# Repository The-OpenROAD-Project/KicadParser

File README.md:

# KicadParser

This is a KiCad file importer/exporter, database, and DRC checker.

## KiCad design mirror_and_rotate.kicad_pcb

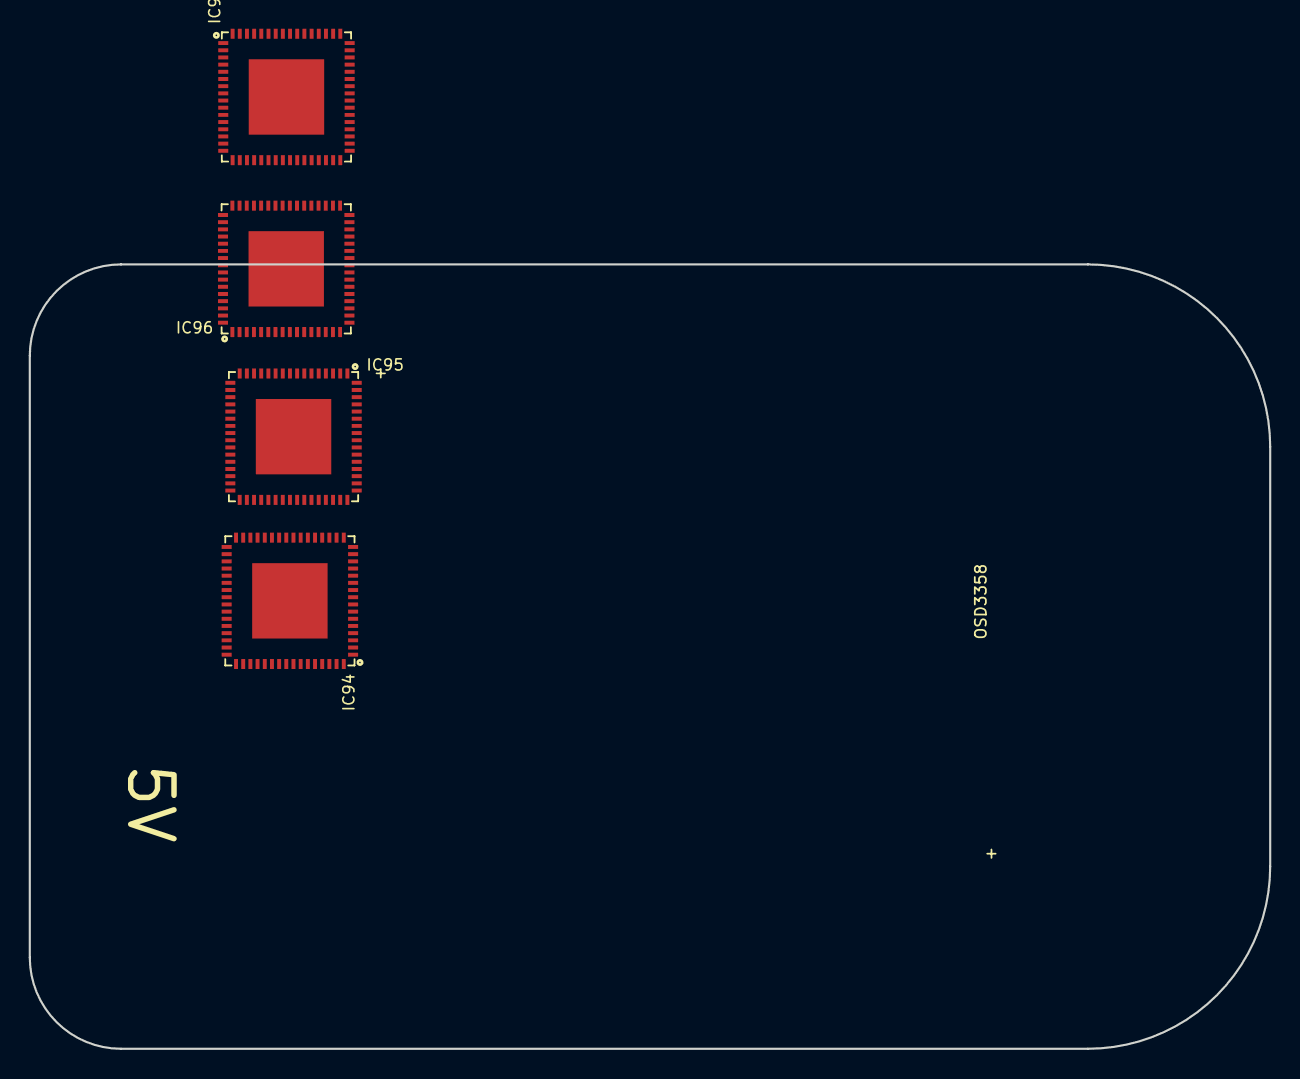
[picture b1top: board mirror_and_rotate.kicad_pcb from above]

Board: 6 copper layers, 86.4 x 54.6 mm, 8 parts (0 on the bottom side), 2 nets, no tracks yet.

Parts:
IC91, IC92, IC93, IC94, IC95, IC96, IC97, IC98: TDA19988BHN/C1,557; SOT804-4(NXP)

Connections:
GND: IC98.8, IC98.9, IC98.16, IC98.17, IC98.18, IC98.19, IC98.53, IC98.54, IC98.61, IC98.62, IC98.63, IC98.65
HDMI_1V8: IC98.5, IC98.14, IC98.29, IC98.35, IC98.36, IC98.41, IC98.46, IC98.47, IC98.48, IC98.55

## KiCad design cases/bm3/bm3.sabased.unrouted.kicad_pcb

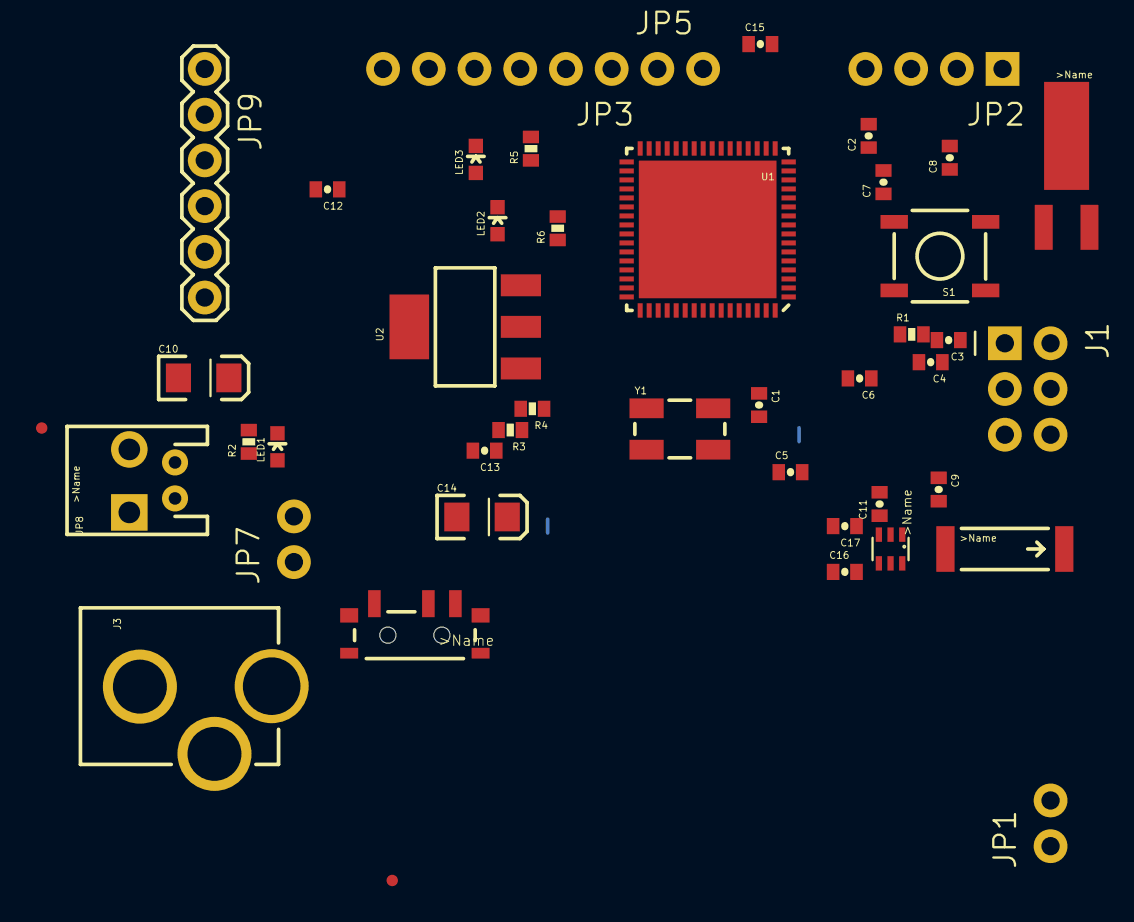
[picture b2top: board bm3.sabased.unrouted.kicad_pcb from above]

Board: 2 copper layers, 48 parts (0 on the bottom side), 41 nets, no tracks yet.

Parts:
A1: ANTENNA2SMD5; ANTENNA-CHIP5
B1: 748421245; BALUN
C1, C2, C3, C4, C12: 1uF; 0402-CAP
C5, C6, C7, C8: 12pF; 0402-CAP
C9: 0.75pF; 0402-CAP
C10, C14: 10uF; EIA3216
C11: 22pF; 0402-CAP
C13, C15: 0.1uF; 0402-CAP
C16, C17: JUMP; 0402-CAP
FID1, FID2: FIDUCIALUFIDUCIAL; MICRO-FIDUCIAL
J1: ISP; 2X3-NS
J3: POWER_JACKPTH_LOCK; POWER_JACK_PTH_LOCK
JP1, JP5, JP7: 1X02_NO_SILK
JP2: 1X04_NO_SILK
JP3: 1X06_NS
JP6: JST-2-PTH
JP8: SCREWTERMINAL-3.5MM-2-NS
JP9: FTDI; FTDI_BASIC
LED1: RED; LED-0603
LED2, LED3: GREEN; LED-0603
R1: 10k; 0402-RES
R2: 1k; 0402-RES
R3: 240; 0402-RES
R4: 390; 0402-RES
R5, R6: 330; 0402-RES
S1: TACTILE_SWITCH_SMD
S2: SWITCH-SPST-SMD-A
SJ1, SJ2: SJ_2S-TRACE
U1: ATMEGA128RFA1; QFN-64
U2: LM1117; SOT223
Y1: 16MHz; CRYSTAL-SMD-5X3
Y2: 32.768kHz; CRYSTAL-32KHZ-SMD

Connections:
3.3V: C3.1, C4.1, C10.A, C12.1, J1.2, JP9.VCC, R1.2, R2.2, R3.2, U1.23, U1.34, U1.44, U1.54, U1.59, U2.2
A6: JP1.1, U1.5
A7: JP1.2, U1.6
AVDD: C1.1, U1.60
CLKI: JP5.1, SJ1.2, U1.33
DTR: C15.1, JP9.DTR
DVDD: C2.1, U1.21, U1.22
FB: R3.1, R4.2, U2.1
GND: B1.5, C1.2, C2.2, C3.2, C4.2, C5.2, C6.2, C7.2, C8.2, C9.1, C10.C, C11.2, C12.2, C13.2, C14.C, J1.6, J3.GND, J3.GNDBREAK, JP6.1, JP7.1, JP8.1, JP9.GND, LED1.C, LED2.C, LED3.C, R4.1, S1.3, SJ1.1, SJ2.1, U1.7, U1.10, U1.20, U1.24, U1.35, U1.45, U1.55, U1.58, U1.61, U1.65
unnamed: LED1.A, R2.1
unnamed: C5.1, U1.57, Y1.3
unnamed: C6.1, U1.56, Y1.1
unnamed: C7.1, U1.18, Y2.X1
unnamed: C8.1, U1.17, Y2.X2
unnamed: B1.2, C11.1
unnamed: LED3.A, R5.1
unnamed: J3.PWR, JP6.2, JP7.2, JP8.2, S2.2
unnamed: B1.4, C16.2
unnamed: B1.3, C17.1
unnamed: LED2.A, R6.1
PB6: R5.2, U1.42
PB7: R6.2, U1.43
PD4: JP3.3, U1.29
PD5: JP3.4, U1.30
PD6: JP3.5, U1.31
PD7: JP3.6, U1.32
PG0: JP2.1, U1.14
PG1: JP2.2, U1.15
PG2: JP2.3, U1.16
PG5: JP2.4, U1.19
RESET: C15.2, J1.5, R1.1, S1.1, U1.12
RFANT: A1.FEED, B1.1, C9.2
RFN: C17.2, U1.9
RFP: C16.1, U1.8
RX0: JP9.TXO, U1.46
RX1: JP3.1, U1.27
SCK: J1.3, U1.37
TST: JP5.2, SJ2.2, U1.11
TX0: JP9.RXI, U1.47
TX1: JP3.2, U1.28
VCC: C13.1, C14.A, S2.1, U2.3

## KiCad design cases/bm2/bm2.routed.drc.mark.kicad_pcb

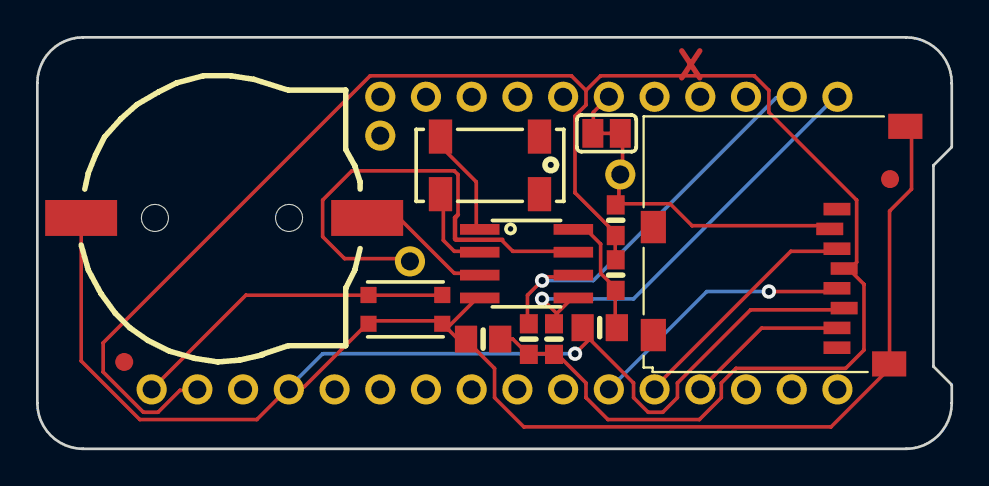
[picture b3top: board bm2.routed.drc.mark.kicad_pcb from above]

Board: 2 copper layers, 50.8 x 22.9 mm, 19 parts (0 on the bottom side), 15 nets.

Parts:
B1: cr1220; CR1220-2
C1, C2: 10uF; 0805-NO
FID1, FID2: FIDUCIAL_1MM
IC1: PCF8523T; SOIC8_150MIL
INT1: 1X01_ROUND
JP1: 1X11_ROUND
JP2: 1X16_ROUND
JP3: 1X01_ROUND
R1, R2: 10K; 0603-NO
R3: 100K; 0603-NO
R4: 1K; 0603-NO
SDCS: 1X01_ROUND
SJ1: SOLDERJUMPER_CLOSEDWIRE
SW1: KMR2; BTN_KMR2_4.6X2.8
X4: microsd; MICROSD
Y1: 32khz; CRYSTAL_8X3.8

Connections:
+3V3: C2.1, JP2.15, R1.2, R2.2, R3.2, R4.1, X4.4
CR1220: B1.+, IC1.3
CS: JP1.6, SJ1.1
GND: B1.-, C1.2, C2.2, IC1.4, JP2.13, SW1.A, SW1.A', X4.6, X4.MT1, X4.MT2
INT1: IC1.7, INT1.1
MISO: JP2.4, X4.7
MOSI: JP2.5, X4.3
unnamed: C1.1, IC1.8, R4.2
unnamed: IC1.1, Y1.P$4
unnamed: IC1.2, Y1.P$1
RESET: JP2.16, SW1.B, SW1.B'
SCK: JP2.6, X4.5
SCL: IC1.6, JP1.10, R2.1
SDA: IC1.5, JP1.11, R1.1
SD_CS: R3.1, SDCS.1, SJ1.2, X4.2

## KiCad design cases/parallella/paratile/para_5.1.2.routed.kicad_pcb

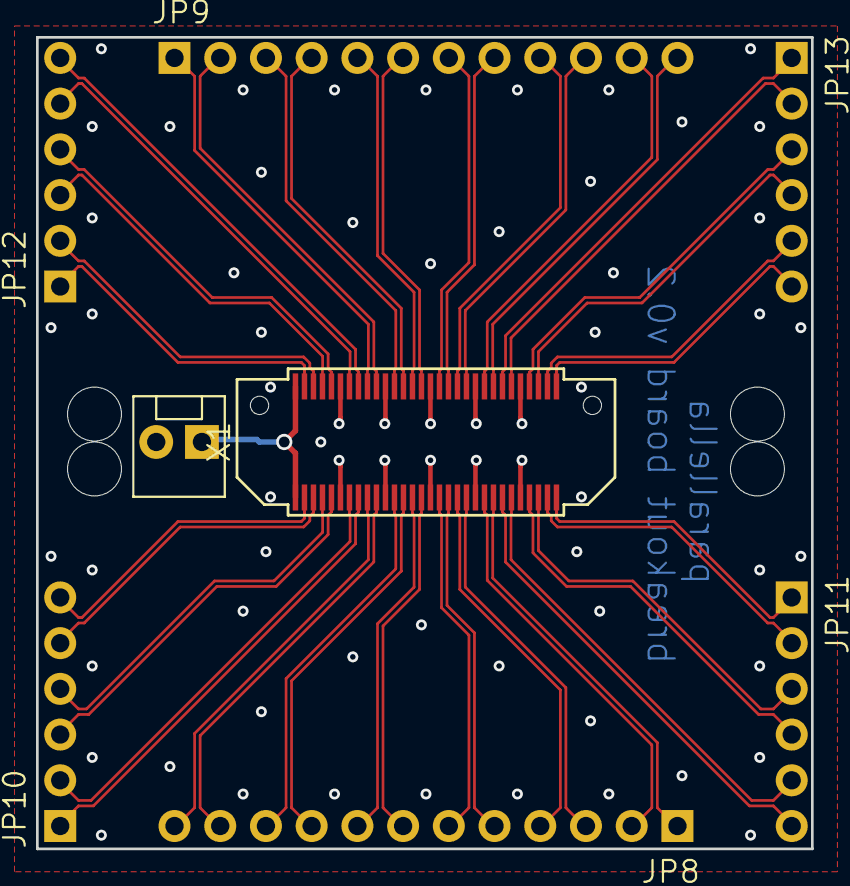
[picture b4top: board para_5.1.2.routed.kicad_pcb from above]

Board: 2 copper layers, 43.1 x 45.1 mm, 13 parts (0 on the bottom side), 50 nets.

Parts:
@HOLE0, @HOLE1, @HOLE2, @HOLE3: (no value)
C2: CAP0805; 0805
JP7: M02POLAR; MOLEX-1X2
JP8, JP9: PINHD-1X12-CB; 1X12-CB
JP10, JP11, JP12, JP13: PINHD-1X6CB; 1X06-CLEANBIG
X1: BTH-030-XX-X-D-A

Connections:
GND: C2.2, JP7.2, X1.11, X1.12, X1.21, X1.22, X1.31, X1.32, X1.41, X1.42, X1.51, X1.52
unnamed: JP8.1, X1.46
unnamed: JP8.2, X1.44
unnamed: JP8.3, X1.40
unnamed: JP8.4, X1.38
unnamed: JP8.5, X1.36
unnamed: JP8.6, X1.34
unnamed: JP8.7, X1.30
unnamed: JP8.8, X1.28
unnamed: JP8.9, X1.26
unnamed: JP8.10, X1.24
unnamed: JP8.11, X1.20
unnamed: JP8.12, X1.18
unnamed: JP9.1, X1.17
unnamed: JP9.2, X1.19
unnamed: JP9.3, X1.23
unnamed: JP9.4, X1.25
unnamed: JP9.5, X1.27
unnamed: JP9.6, X1.29
unnamed: JP9.7, X1.33
unnamed: JP9.8, X1.35
unnamed: JP9.9, X1.37
unnamed: JP9.10, X1.39
unnamed: JP9.11, X1.43
unnamed: JP9.12, X1.45
unnamed: JP10.1, X1.16
unnamed: JP10.2, X1.14
unnamed: JP10.3, X1.10
unnamed: JP10.4, X1.8
unnamed: JP10.5, X1.6
unnamed: JP10.6, X1.4
unnamed: JP11.1, X1.60
unnamed: JP11.2, X1.58
unnamed: JP11.3, X1.56
unnamed: JP11.4, X1.54
unnamed: JP11.5, X1.50
unnamed: JP11.6, X1.48
unnamed: JP12.1, X1.3
unnamed: JP12.2, X1.5
unnamed: JP12.3, X1.7
unnamed: JP12.4, X1.9
unnamed: JP12.5, X1.13
unnamed: JP12.6, X1.15
unnamed: JP13.1, X1.47
unnamed: JP13.2, X1.49
unnamed: JP13.3, X1.53
unnamed: JP13.4, X1.55
unnamed: JP13.5, X1.57
unnamed: JP13.6, X1.59
VCC: C2.1, JP7.1, X1.1, X1.2

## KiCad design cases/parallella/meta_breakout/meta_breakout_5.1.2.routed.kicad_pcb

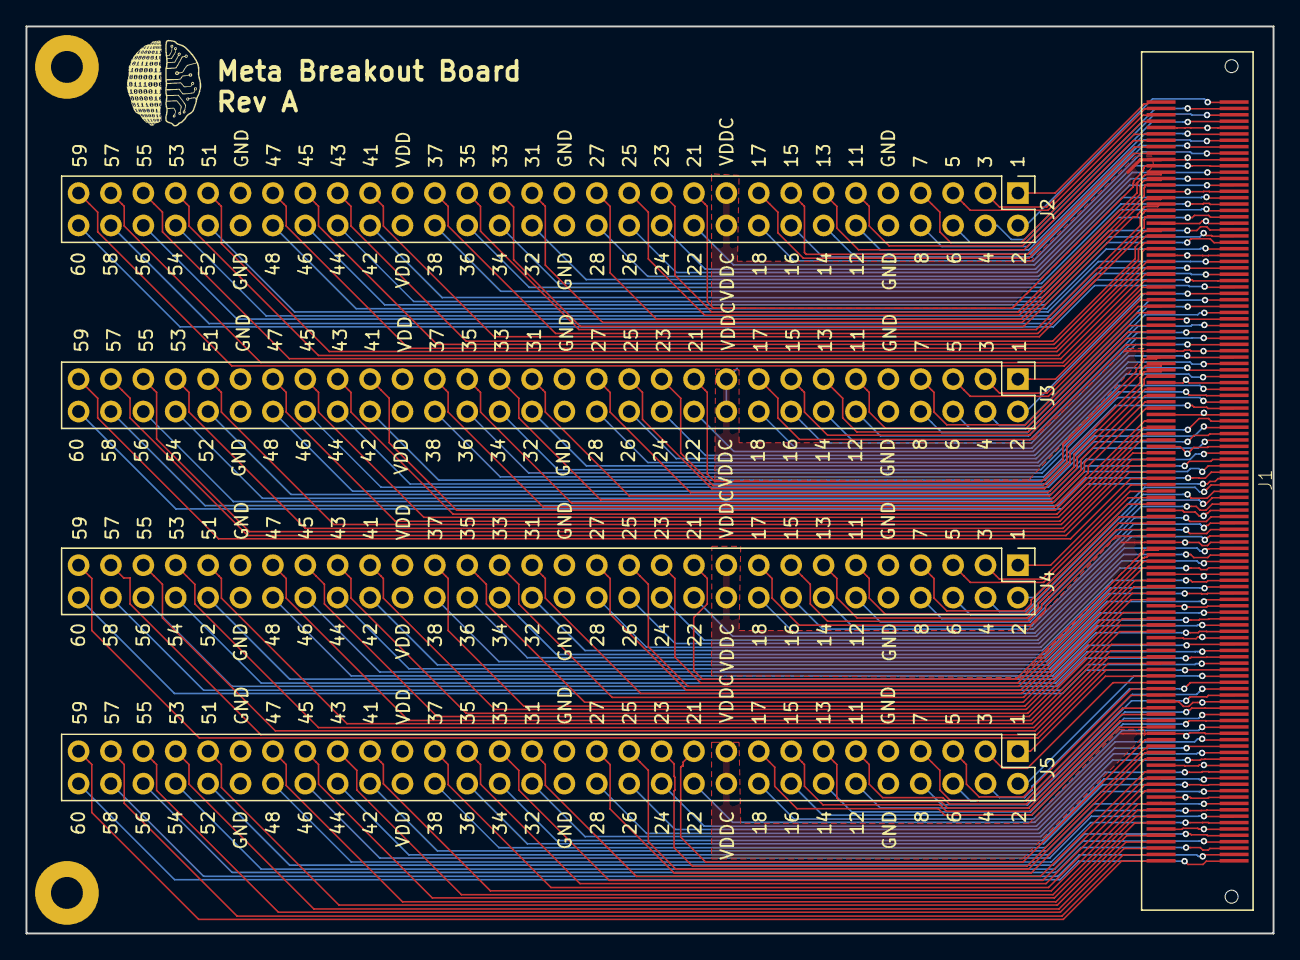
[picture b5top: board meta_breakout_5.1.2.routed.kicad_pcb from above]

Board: 4 copper layers, 97.8 x 71.1 mm, 5 parts (0 on the bottom side), 209 nets.

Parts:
J1: BSH-120; BSH-120-01-X-D-A
J2, J3, J4, J5: Conn_02x30_Odd_Even; PinHeader_2x30_P2.54mm_Vertical

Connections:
/CTRL_IN0: J1.59, J2.59
/CTRL_IN1: J1.119, J3.59
/CTRL_IN2: J1.179, J4.59
/CTRL_IN3: J1.239, J5.59
/CTRL_OUT0: J1.60, J2.60
/CTRL_OUT1: J1.120, J3.60
/CTRL_OUT2: J1.180, J4.60
/CTRL_OUT3: J1.240, J5.60
/DATA_IN_N0: J1.21, J2.21
/DATA_IN_N1: J1.25, J2.25
/DATA_IN_N2: J1.31, J2.31
/DATA_IN_N3: J1.35, J2.35
/DATA_IN_N4: J1.41, J2.41
/DATA_IN_N5: J1.45, J2.45
/DATA_IN_N6: J1.51, J2.51
/DATA_IN_N7: J1.55, J2.55
/DATA_IN_N8: J1.81, J3.21
/DATA_IN_N9: J1.85, J3.25
/DATA_IN_N10: J1.91, J3.31
/DATA_IN_N11: J1.95, J3.35
/DATA_IN_N12: J1.101, J3.41
/DATA_IN_N13: J1.105, J3.45
/DATA_IN_N14: J1.111, J3.51
/DATA_IN_N15: J1.115, J3.55
/DATA_IN_N16: J1.141, J4.21
/DATA_IN_N17: J1.145, J4.25
/DATA_IN_N18: J1.151, J4.31
/DATA_IN_N19: J1.155, J4.35
/DATA_IN_N20: J1.161, J4.41
/DATA_IN_N21: J1.165, J4.45
/DATA_IN_N22: J1.171, J4.51
/DATA_IN_N23: J1.175, J4.55
/DATA_IN_N24: J1.201, J5.21
/DATA_IN_N25: J1.205, J5.25
/DATA_IN_N26: J1.211, J5.31
/DATA_IN_N27: J1.215, J5.35
/DATA_IN_N28: J1.221, J5.41
/DATA_IN_N29: J1.225, J5.45
/DATA_IN_N30: J1.231, J5.51
/DATA_IN_N31: J1.235, J5.55
/DATA_IN_P0: J1.23, J2.23
/DATA_IN_P1: J1.27, J2.27
/DATA_IN_P2: J1.33, J2.33
/DATA_IN_P3: J1.37, J2.37
/DATA_IN_P4: J1.43, J2.43
/DATA_IN_P5: J1.47, J2.47
/DATA_IN_P6: J1.53, J2.53
/DATA_IN_P7: J1.57, J2.57
/DATA_IN_P8: J1.83, J3.23
/DATA_IN_P9: J1.87, J3.27
/DATA_IN_P10: J1.93, J3.33
/DATA_IN_P11: J1.97, J3.37
/DATA_IN_P12: J1.103, J3.43
/DATA_IN_P13: J1.107, J3.47
/DATA_IN_P14: J1.113, J3.53
/DATA_IN_P15: J1.117, J3.57
/DATA_IN_P16: J1.143, J4.23
/DATA_IN_P17: J1.147, J4.27
/DATA_IN_P18: J1.153, J4.33
/DATA_IN_P19: J1.157, J4.37
/DATA_IN_P20: J1.163, J4.43
/DATA_IN_P21: J1.167, J4.47
/DATA_IN_P22: J1.173, J4.53
/DATA_IN_P23: J1.177, J4.57
/DATA_IN_P24: J1.203, J5.23
/DATA_IN_P25: J1.207, J5.27
/DATA_IN_P26: J1.213, J5.33
/DATA_IN_P27: J1.217, J5.37
/DATA_IN_P28: J1.223, J5.43
/DATA_IN_P29: J1.227, J5.47
/DATA_IN_P30: J1.233, J5.53
/DATA_IN_P31: J1.237, J5.57
/DATA_OUT_N0: J1.22, J2.22
/DATA_OUT_N1: J1.26, J2.26
/DATA_OUT_N2: J1.32, J2.32
/DATA_OUT_N3: J1.36, J2.36
/DATA_OUT_N4: J1.42, J2.42
/DATA_OUT_N5: J1.46, J2.46
/DATA_OUT_N6: J1.52, J2.52
/DATA_OUT_N7: J1.56, J2.56
/DATA_OUT_N8: J1.82, J3.22
/DATA_OUT_N9: J1.86, J3.26
/DATA_OUT_N10: J1.92, J3.32
/DATA_OUT_N11: J1.96, J3.36
/DATA_OUT_N12: J1.102, J3.42
/DATA_OUT_N13: J1.106, J3.46
/DATA_OUT_N14: J1.112, J3.52
/DATA_OUT_N15: J1.116, J3.56
/DATA_OUT_N16: J1.142, J4.22
/DATA_OUT_N17: J1.146, J4.26
/DATA_OUT_N18: J1.152, J4.32
/DATA_OUT_N19: J1.156, J4.36
/DATA_OUT_N20: J1.162, J4.42
/DATA_OUT_N21: J1.166, J4.46
/DATA_OUT_N22: J1.172, J4.52
/DATA_OUT_N23: J1.176, J4.56
/DATA_OUT_N24: J1.202, J5.22
/DATA_OUT_N25: J1.206, J5.26
/DATA_OUT_N26: J1.212, J5.32
/DATA_OUT_N27: J1.216, J5.36
/DATA_OUT_N28: J1.222, J5.42
/DATA_OUT_N29: J1.226, J5.46
/DATA_OUT_N30: J1.232, J5.52
/DATA_OUT_N31: J1.236, J5.56
/DATA_OUT_P0: J1.24, J2.24
/DATA_OUT_P1: J1.28, J2.28
/DATA_OUT_P2: J1.34, J2.34
/DATA_OUT_P3: J1.38, J2.38
/DATA_OUT_P4: J1.44, J2.44
/DATA_OUT_P5: J1.48, J2.48
/DATA_OUT_P6: J1.54, J2.54
/DATA_OUT_P7: J1.58, J2.58
/DATA_OUT_P8: J1.84, J3.24
/DATA_OUT_P9: J1.88, J3.28
/DATA_OUT_P10: J1.94, J3.34
/DATA_OUT_P11: J1.98, J3.38
/DATA_OUT_P12: J1.104, J3.44
/DATA_OUT_P13: J1.108, J3.48
/DATA_OUT_P14: J1.114, J3.54
/DATA_OUT_P15: J1.118, J3.58
/DATA_OUT_P16: J1.144, J4.24
/DATA_OUT_P17: J1.148, J4.28
/DATA_OUT_P18: J1.154, J4.34
/DATA_OUT_P19: J1.158, J4.38
/DATA_OUT_P20: J1.164, J4.44
/DATA_OUT_P21: J1.168, J4.48
/DATA_OUT_P22: J1.174, J4.54
/DATA_OUT_P23: J1.178, J4.58
/DATA_OUT_P24: J1.204, J5.24
/DATA_OUT_P25: J1.208, J5.28
/DATA_OUT_P26: J1.214, J5.34
/DATA_OUT_P27: J1.218, J5.38
/DATA_OUT_P28: J1.224, J5.44
/DATA_OUT_P29: J1.228, J5.48
/DATA_OUT_P30: J1.234, J5.54
/DATA_OUT_P31: J1.238, J5.58
/FRAME_IN_N0: J1.5, J2.5
/FRAME_IN_N1: J1.65, J3.5
/FRAME_IN_N2: J1.125, J4.5
/FRAME_IN_N3: J1.185, J5.5
/FRAME_IN_P0: J1.7, J2.7
/FRAME_IN_P1: J1.67, J3.7
/FRAME_IN_P2: J1.127, J4.7
/FRAME_IN_P3: J1.187, J5.7
/FRAME_OUT_N0: J1.6, J2.6
/FRAME_OUT_N1: J1.66, J3.6
/FRAME_OUT_N2: J1.126, J4.6
/FRAME_OUT_N3: J1.186, J5.6
/FRAME_OUT_P0: J1.8, J2.8
/FRAME_OUT_P1: J1.68, J3.8
/FRAME_OUT_P2: J1.128, J4.8
/FRAME_OUT_P3: J1.188, J5.8
/GND: J1.9, J1.10, J1.29, J1.30, J1.49, J1.50, J1.69, J1.70, J1.89, J1.90, J1.109, J1.110, J1.129, J1.130, J1.149, J1.150, J1.169, J1.170, J1.189, J1.190, J1.209, J1.210, J1.229, J1.230, J2.9, J2.10, J2.29, J2.30, J2.49, J2.50, J3.9, J3.10, J3.29, J3.30, J3.49, J3.50, J4.9, J4.10, J4.29, J4.30, J4.49, J4.50, J5.9, J5.10, J5.29, J5.30, J5.49, J5.50
/LCLK_IN_N0: J1.1, J2.1
/LCLK_IN_N1: J1.61, J3.1
/LCLK_IN_N2: J1.121, J4.1
/LCLK_IN_N3: J1.181, J5.1
/LCLK_IN_P0: J1.3, J2.3
/LCLK_IN_P1: J1.63, J3.3
/LCLK_IN_P2: J1.123, J4.3
/LCLK_IN_P3: J1.183, J5.3
/LCLK_OUT_N0: J1.2, J2.2
/LCLK_OUT_N1: J1.62, J3.2
/LCLK_OUT_N2: J1.122, J4.2
/LCLK_OUT_N3: J1.182, J5.2
/LCLK_OUT_P0: J1.4, J2.4
/LCLK_OUT_P1: J1.64, J3.4
/LCLK_OUT_P2: J1.124, J4.4
/LCLK_OUT_P3: J1.184, J5.4
/VDD0: J1.19, J1.20, J2.19, J2.20
/VDD1: J1.79, J1.80, J3.19, J3.20
/VDD2: J1.139, J1.140, J4.19, J4.20
/VDD3: J1.199, J1.200, J5.19, J5.20
/VDDIO0: J1.39, J1.40, J2.39, J2.40
/VDDIO1: J1.99, J1.100, J3.39, J3.40
/VDDIO2: J1.159, J1.160, J4.39, J4.40
/VDDIO3: J1.219, J1.220, J5.39, J5.40
/WAIT_RD_IN_N0: J1.16, J2.16
/WAIT_RD_IN_N1: J1.76, J3.16
/WAIT_RD_IN_N2: J1.136, J4.16
/WAIT_RD_IN_N3: J1.196, J5.16
/WAIT_RD_IN_P0: J1.18, J2.18
/WAIT_RD_IN_P1: J1.78, J3.18
/WAIT_RD_IN_P2: J1.138, J4.18
/WAIT_RD_IN_P3: J1.198, J5.18
/WAIT_RD_OUT_N0: J1.15, J2.15
/WAIT_RD_OUT_N1: J1.75, J3.15
/WAIT_RD_OUT_N2: J1.135, J4.15
/WAIT_RD_OUT_N3: J1.195, J5.15
/WAIT_RD_OUT_P0: J1.17, J2.17
/WAIT_RD_OUT_P1: J1.77, J3.17
/WAIT_RD_OUT_P2: J1.137, J4.17
/WAIT_RD_OUT_P3: J1.197, J5.17
/WAIT_WR_IN_N0: J1.12, J2.12
/WAIT_WR_IN_N1: J1.72, J3.12
/WAIT_WR_IN_N2: J1.132, J4.12
/WAIT_WR_IN_N3: J1.192, J5.12
/WAIT_WR_IN_P0: J1.14, J2.14
/WAIT_WR_IN_P1: J1.74, J3.14
/WAIT_WR_IN_P2: J1.134, J4.14
/WAIT_WR_IN_P3: J1.194, J5.14
/WAIT_WR_OUT_N0: J1.11, J2.11
/WAIT_WR_OUT_N1: J1.71, J3.11
/WAIT_WR_OUT_N2: J1.131, J4.11
/WAIT_WR_OUT_N3: J1.191, J5.11
/WAIT_WR_OUT_P0: J1.13, J2.13
/WAIT_WR_OUT_P1: J1.73, J3.13
/WAIT_WR_OUT_P2: J1.133, J4.13
/WAIT_WR_OUT_P3: J1.193, J5.13

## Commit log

2019-08-13 addAPIs
2019-08-13 addMakefile
2019-08-16 Add router helping APIs
2019-08-16 Overload net::getId()
2019-08-16 get PcbRouterInfo based on netId
2019-09-04 Use Cmake and restructure folders
2019-09-05 Clean the CMakeLists.txt
2019-09-05 -Wall option in CMakeLists.txt
2019-09-07 add segment/via; fix bug for boundary/rotation
2019-09-09 indent
2019-09-09 add license
2019-09-12 refactor
2019-09-12 restructure
2019-09-13 VS Code beautifier and input file extension checking
2019-09-13 VS Code beautifier, util.h updates and basic file extension checking
2019-09-13 Update #define guard
2019-09-13 add testcases
2019-09-14 Minor refactors
2019-09-14 Fix warning messages
2019-09-16 Refactor and code review
2019-09-16 Add new artificial testcase for router testing Vias and Rip-up & Reroute
2019-09-19 Add APIs and major refactor
2019-09-20 add via and segment header
2019-09-20 modify APIs
2019-09-20 Add more APIs and minor refactors
2019-09-21 APIs and minor refactors
2019-09-23 Add segments and vias
2019-09-23 Minor refactors on APIs
2019-09-24 Add APIs for pads' width and height
2019-09-24 Update mymath.h to point.h and use template
2019-09-25 Add APIs in point.h
2019-09-25 unconnected pins
2019-09-25 Fix template type T
2019-09-26 boundary and octagon
2019-09-27 add testcase
2019-09-28 test meta_breakout, fix seg fault
2019-09-28 Add parallella testcases in .kicad_pcb format
2019-09-28 Add three more parallella testcases
2019-09-28 Change parallella files into routed and unrouted ones
2019-09-28 0.1 version of printing out .kicad_pcb
2019-09-28 fix via for parallella
2019-09-30 Fix layer from Component to Instance and from Padstack to Pin
2019-10-03 Deprecate the layers information in Pin
2019-10-03 modify shape func
2019-10-04 New formatter to follow the OpenROAD 's guidance and API in Point_3D
2019-10-05 Fix distance function in point.h
2019-10-06 Use Point_3D<int> as Location in the router
2019-10-11 Add API for getting netclasses
2019-10-12 write kicad pcb
2019-10-12 add module position, angle...
2019-10-12 setLayer for inst
2019-10-18 Add bm2 routing result from our router. Remove autosave kicad file.
2019-10-18 Add our routing result with merged segments on testcase bm2
2019-10-18 Remove redundant testcase
2019-10-19 Comment out unused header file <optional>
2019-10-20 modify octagon
2019-10-23 add bbox
2019-10-24 add drc
2019-10-24 merge
2019-10-25 Add Devon's DDR3 cases
2019-10-25 Minor refactors and VS code beautifier
2019-10-30 mark drcs
2019-10-30 add marked drc testcases
2019-11-01 VSC beautifier on shape.*
2019-11-01 Add SA-based placement on bm3 testcase
2019-11-01 add boost in database
2019-11-01 Fix shape_to_coords() and padstack. VSC beautifier on srcs.
2019-11-02 Fix padstack's shape polygon. Add API for debugging Boost Polygons.
2019-11-03 getPinShapeRelativeCoordsToModule
2019-11-13 FolderName and fileName for printKiCad()
2019-11-14 add equations to object
2019-11-14 Fix the bug of output directory
2019-11-14 write tree
2019-11-16 git segment and via
2019-11-18 locked instance
2019-11-25 modify parser
2019-11-25 printinst
2019-11-25 VSC beautifier. Add APIs for removing all routed nets and report routed nets statistics.
2019-11-25 Diasable writing out parsing tree.
2019-11-26 locked inst
2019-11-27 print obj
2019-11-27 Add API for Design statistics
2019-12-05 CMake swig compatibility
2019-12-10 Add bm14 testcse. Update .gitignore
2019-12-11 Fix Oval shape in shape_to_coords. Apply VSCode beautifier to that source.
2019-12-11 Fix SWIG integration and add PcbDB.i
2019-12-11 Add PcbDB.i
2019-12-11 Count 'power' key word as conductor layer
2019-12-11 Fix the SWIG Integration
2019-12-11 Syntax in CMakeLists.txt
2019-12-11 moore compat
2019-12-11 rm garbage files, sorry
2019-12-11 .i and garbage files ignore
2019-12-12 via octagon
2019-12-14 Support 2-sided component pin location and VSC beautifier
2019-12-18 Update CMakeLists.txt
    simplify swig check
2019-12-18 python 3 conversion
2019-12-30 shape circle to octagon
2020-01-08 fix kicad writer for pad
2020-01-08 db angled bracket spacing
2020-01-08 bracket spacing
2020-01-08 fix pad rotation
2020-01-09 deprecated getBoundary
2020-01-09 edge cut boundary
2020-01-09 moore dep not work fix
2020-01-09 printKiCad() set full output filename via 3rd argument
2020-01-09 two-sided courtyards
2020-01-09 Update boardBoundaryByEdgeCuts to consider edge width
2020-01-18 add <= for point
2020-02-04 Add supports of MICRO and BLIND_BURIED vias
2020-02-04 VS code beautifier on kicadPcbDataBase.cpp
2020-02-04 Writer supports micro/blind/buried vias
2020-02-04 APIs for Via
2020-02-11 Options for outputing debug information of API printKiCad
2020-02-12 add locked attribute
2020-02-13 Output via drill when printKiCad
2020-03-19 buildFlippedComponent fn flips each element of component abt local y axis
2020-03-25 bus ilp
2020-03-25 second comp instantiation
2020-03-28 update pin layer for writer
2020-03-30 layer change exp
2020-03-30 couple position typos
2020-03-30 another test
2020-03-31 update pin position for mirror instance in writer
2020-03-31 pull changes
2020-03-31 comp id pair & pad's position bug
2020-04-16 comment out pin location in writer
2020-04-16 add segments
2020-05-24 bus, micro via
2020-05-26 bbox u
2020-07-16 checker
